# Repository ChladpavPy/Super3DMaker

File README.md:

# Super3DMaker Controller Board

So first I want to explain, why I started this project. I had an old Profi3DMaker 3D printer at home, which was not used for a long time, mainly because of the hardware, which was just outdated. Because the printer had electronics probably from years like 2012 and older, it was my idea to bring it again to life, because the tech of 3D printing and electronics changed a lot. The 3D printer actually works, but does not stand a chance to modern machines which would be even cheaper based on the materials. Back in 2012, this printer was high-end and one of the most expensive 3D printers, you could get, because of the high quality aluminium frame, but because the technology changed so rapidly, it is just unreliable and prints items badly now, when compared to new 3d printers, which are also cheap. And because it is mainly and electronics issue, I realized that I could build my own new 3D printer board for this 3D printer and bring it again to life, so I started new Project.

The first stage was actually reverse-engineering the old board and studying as much possible of how modern 3d printers work.

A custom mainboard designed to replace the old electronics in my 3D printer. Built to handle klipper high speed kinematics and communicate directly with a Raspberry Pi Zero 2W. Designed entirely from scratch in KiCad 10.

## The Build and Integration Phase

After receiving the manufactured PCB from JLCPCB, the project transitioned into the physical build phase. This involved soldering all components and integrating the new board into the chassis. 

The most intensive part was the software setup and calibration. I configured Klipper and the Raspberry Pi, and spent a significant amount of time getting the `printer.cfg` right. This meant dialing in the correct motor parameters, gear ratios, and microsteps through trial and error and reverse engineering.

### Results and Current Limitations

The custom STM32F407VET6 board works perfectly and successfully replaces the old ATmega setup. Klipper brings many modern features compared to the old Marlin firmware. Thanks to the new TMC2209 drivers, the printer is now significantly quieter during operation.

However, the build process revealed several mechanical limitations of the original Profi3DMaker chassis that the new electronics alone cannot fix:
* **Z-Axis Noise:** Despite the silent drivers, the Z-axis still makes mechanical grinding noises, indicating a physical issue with the leadscrews or bearings.
* **Heated Bed Inefficiency:** The massive original heated bed takes around an hour to reach just 70°C. 
* **Toolhead Weight:** The older extruder system is extremely heavy, limiting printing speeds and precision. 

To fully utilize the new controller board's capabilities, I have designed a completely new mount for a modern toolhead. This can be actually directly mounted on the chassis. However, this will only add weight if I don't disassemble the moving carriage from the tubes, which requires practically disassembling the entire printer, which I plan to do as a future upgrade. This would also require creating another model which would replace the previous aluminium carriage on the tubes. For now, the goal of successfully designing, building, and running a custom controller board has been achieved.

## Firmware

Since this board is built around a custom STM32F407VET6 microcontroller, it runs on the open-source [Klipper](https://github.com/Klipper3d/klipper) firmware. Instead of writing custom kinematic calculations from scratch, the firmware setup uses a printer configuration file. You can find the complete pin-mapping and configuration file (`printer.cfg`), along with the original dumped `.srec` firmware files used to reverse-engineer the correct gear ratios and microsteps, ready in the `Firmware` folder. You can also access all the other original files for this 3D printer by registering on the 3D Factories website.
## Project Features

* **Microcontroller:** STM32F407VET6 (100-pin, 32-bit ARM Cortex-M4)
* **Stackup:** 4-Layer PCB (Signal / GND / GND / Signal) for internal routing and better EMI shielding
* **Stepper Drivers:** 6x UART-controlled TMC2209 sockets
* **Power:** 24V main input with dual LM2596S buck converters (5V and 3.3V rails)
* **Connectivity:** USB-B for main communication, native Raspberry Pi UART interface
* **Displays:** Standard 10-pin IDC EXP1 and EXP2 headers for legacy 12864 or modern SPI BTT Mini12864 displays
* **Hardware Interlock:** Laser module power logically tied to the high-current heated bed circuit to prevent simultaneous power draw

* And more other...

### Video Demos

https://github.com/user-attachments/assets/c8a4d6e0-8937-4ded-b093-ac17ca0ef771

https://github.com/user-attachments/assets/72c90019-3e0b-4c00-92d0-47ec632bfb1b

https://github.com/user-attachments/assets/8aad29d0-d306-4471-a87c-c93d6b09ec2d

LIS2DW accelometer calibration

https://github.com/user-attachments/assets/c06aa969-909b-4192-8ba1-088b3594a9f0

CR Touch Bed Mesh

https://github.com/user-attachments/assets/029f4fde-3b9d-4758-a506-7faca7a6295e

## Gallery

### Build Preview

### Printing

### 3D PCB Render

### PCB Routing

### Schematic

---

## Bill of Materials (BOM)

| Component | Qty | Purpose / Description | Price (USD) | Link / Distributor |
| :--- | :---: | :--- | :--- | :--- |
| **Custom PCBA (Mainboard)** | 2 | Custom designed 4-layer STM32 controller board. Fully assembled via JLCPCB SMT (minus the THT USB-B connector which will be soldered manually to avoid mechanical case collisions). | ~$137.67 | JLCPCB - This is the price for 2 assembled boards to keep the price as low as possible. |
| **BIQU H2 V2S REVO** | 1 | Ultra-lightweight direct drive extrusion system with rapid-change nozzle capability. Replaces the current heavy toolhead, significantly reducing weight on the massive 400mm X-axis for faster, vibration-free printing. | $151.45 | [Allegro](https://allegro.cz/produkt/extruder-btt-biqu-h2-v2s-revo-direct-drive-1-75-mm-ce63ae7c-46b2-4eb6-95d3-a286495341f3?offerId=12801178318) |
| **ADXL345 3-Axis Accelerometer** | 2 | Essential for Klipper's Input Shaping calibration. It measures the physical resonance frequencies of the X and Y axes, allowing the firmware to actively cancel out vibrations during high-speed printing and eliminate ringing/ghosting on the printed parts. | $2.88 | [AliExpress](https://a.aliexpress.com/_EH7aAa2) |
| **CR-Touch (Auto Bed Leveling)** | 1 | Provides automatic high-precision mesh bed leveling. It compensates for any slight warping of the print bed and ensures a perfect first layer every time by measuring the distance between the nozzle and the build surface at multiple points. | $20.00 | [AliExpress](https://a.aliexpress.com/_EvwN6HC) |
| **BigTreeTech TMC2209 V1.3** | 6 | These are high-performance silent motor drivers required for the custom motherboard. They feature StealthChop technology for near-silent operation and StallGuard for sensorless homing, eliminating the need for physical limit switches. | $19.25 | [AliExpress](https://a.aliexpress.com/_EILgKrG) |
| **Raspberry Pi Zero 2W** | 1 | Serves as the main host computer for the custom 3D printer. It runs the Klipper firmware ecosystem and its web interface (Mainsail/Fluidd), performs heavy kinematics calculations, and sends precise hardware commands to the custom-designed STM32 motherboard via serial/USB connection. | $20.17 | [Rpishop](https://rpishop.cz/raspberry-pi-zero/4311-raspberry-pi-zero-2-w.html) |

### Mechanical and Assembly

| Item | Qty | Specification | Purpose |
| :--- | :---: | :--- | :--- |
| **Original Aluminum Case** | 1 | The heavy original printer chassis | I had to reverse engineer the mounting holes and connector distances, because I could not get the original CAD files. It was a nightmare but it fits within like 4.7mm of the board edge now. |
| **M3 Screws** | 4 | Standard mounting hardware | Securing the PCB to the chassis standoffs. |
- For the case of the 3d printer - Profi3DMaker case is used

## How to Build and Flash Firmware

If you want to replicate this custom controller board for your own Profi3DMaker or similar 3D printer, follow these steps:

1. **PCB Fabrication & Assembly:** Use the provided Gerber files (found in the repository) to manufacture the board. Most SMD components are assembled by JLCPCB, but you will need to manually solder the THT USB-B connector, terminal blocks, and JST headers.
2. **STM32 Bootloader & Klipper Firmware:**
   * Connect the board to your PC via USB-B while holding the BOOT/RESET buttons to enter DFU mode.
   * Compile Klipper for the `STM32F407VET6` chip using `make menuconfig` on your Raspberry Pi Zero 2W.
   * Flash the compiled `klipper.bin` to the STM32 using STM32CubeProgrammer.
3. **Raspberry Pi Integration:** Connect the Raspberry Pi Zero 2W to the board using the dedicated UART pins for serial communication.
4. **Configuration:** Upload the provided `printer.cfg` (found in the `/Firmware` folder) to your Klipper interface (Mainsail/Fluidd) and verify motor directions and sensor readings.
That is all, thank you for reading!

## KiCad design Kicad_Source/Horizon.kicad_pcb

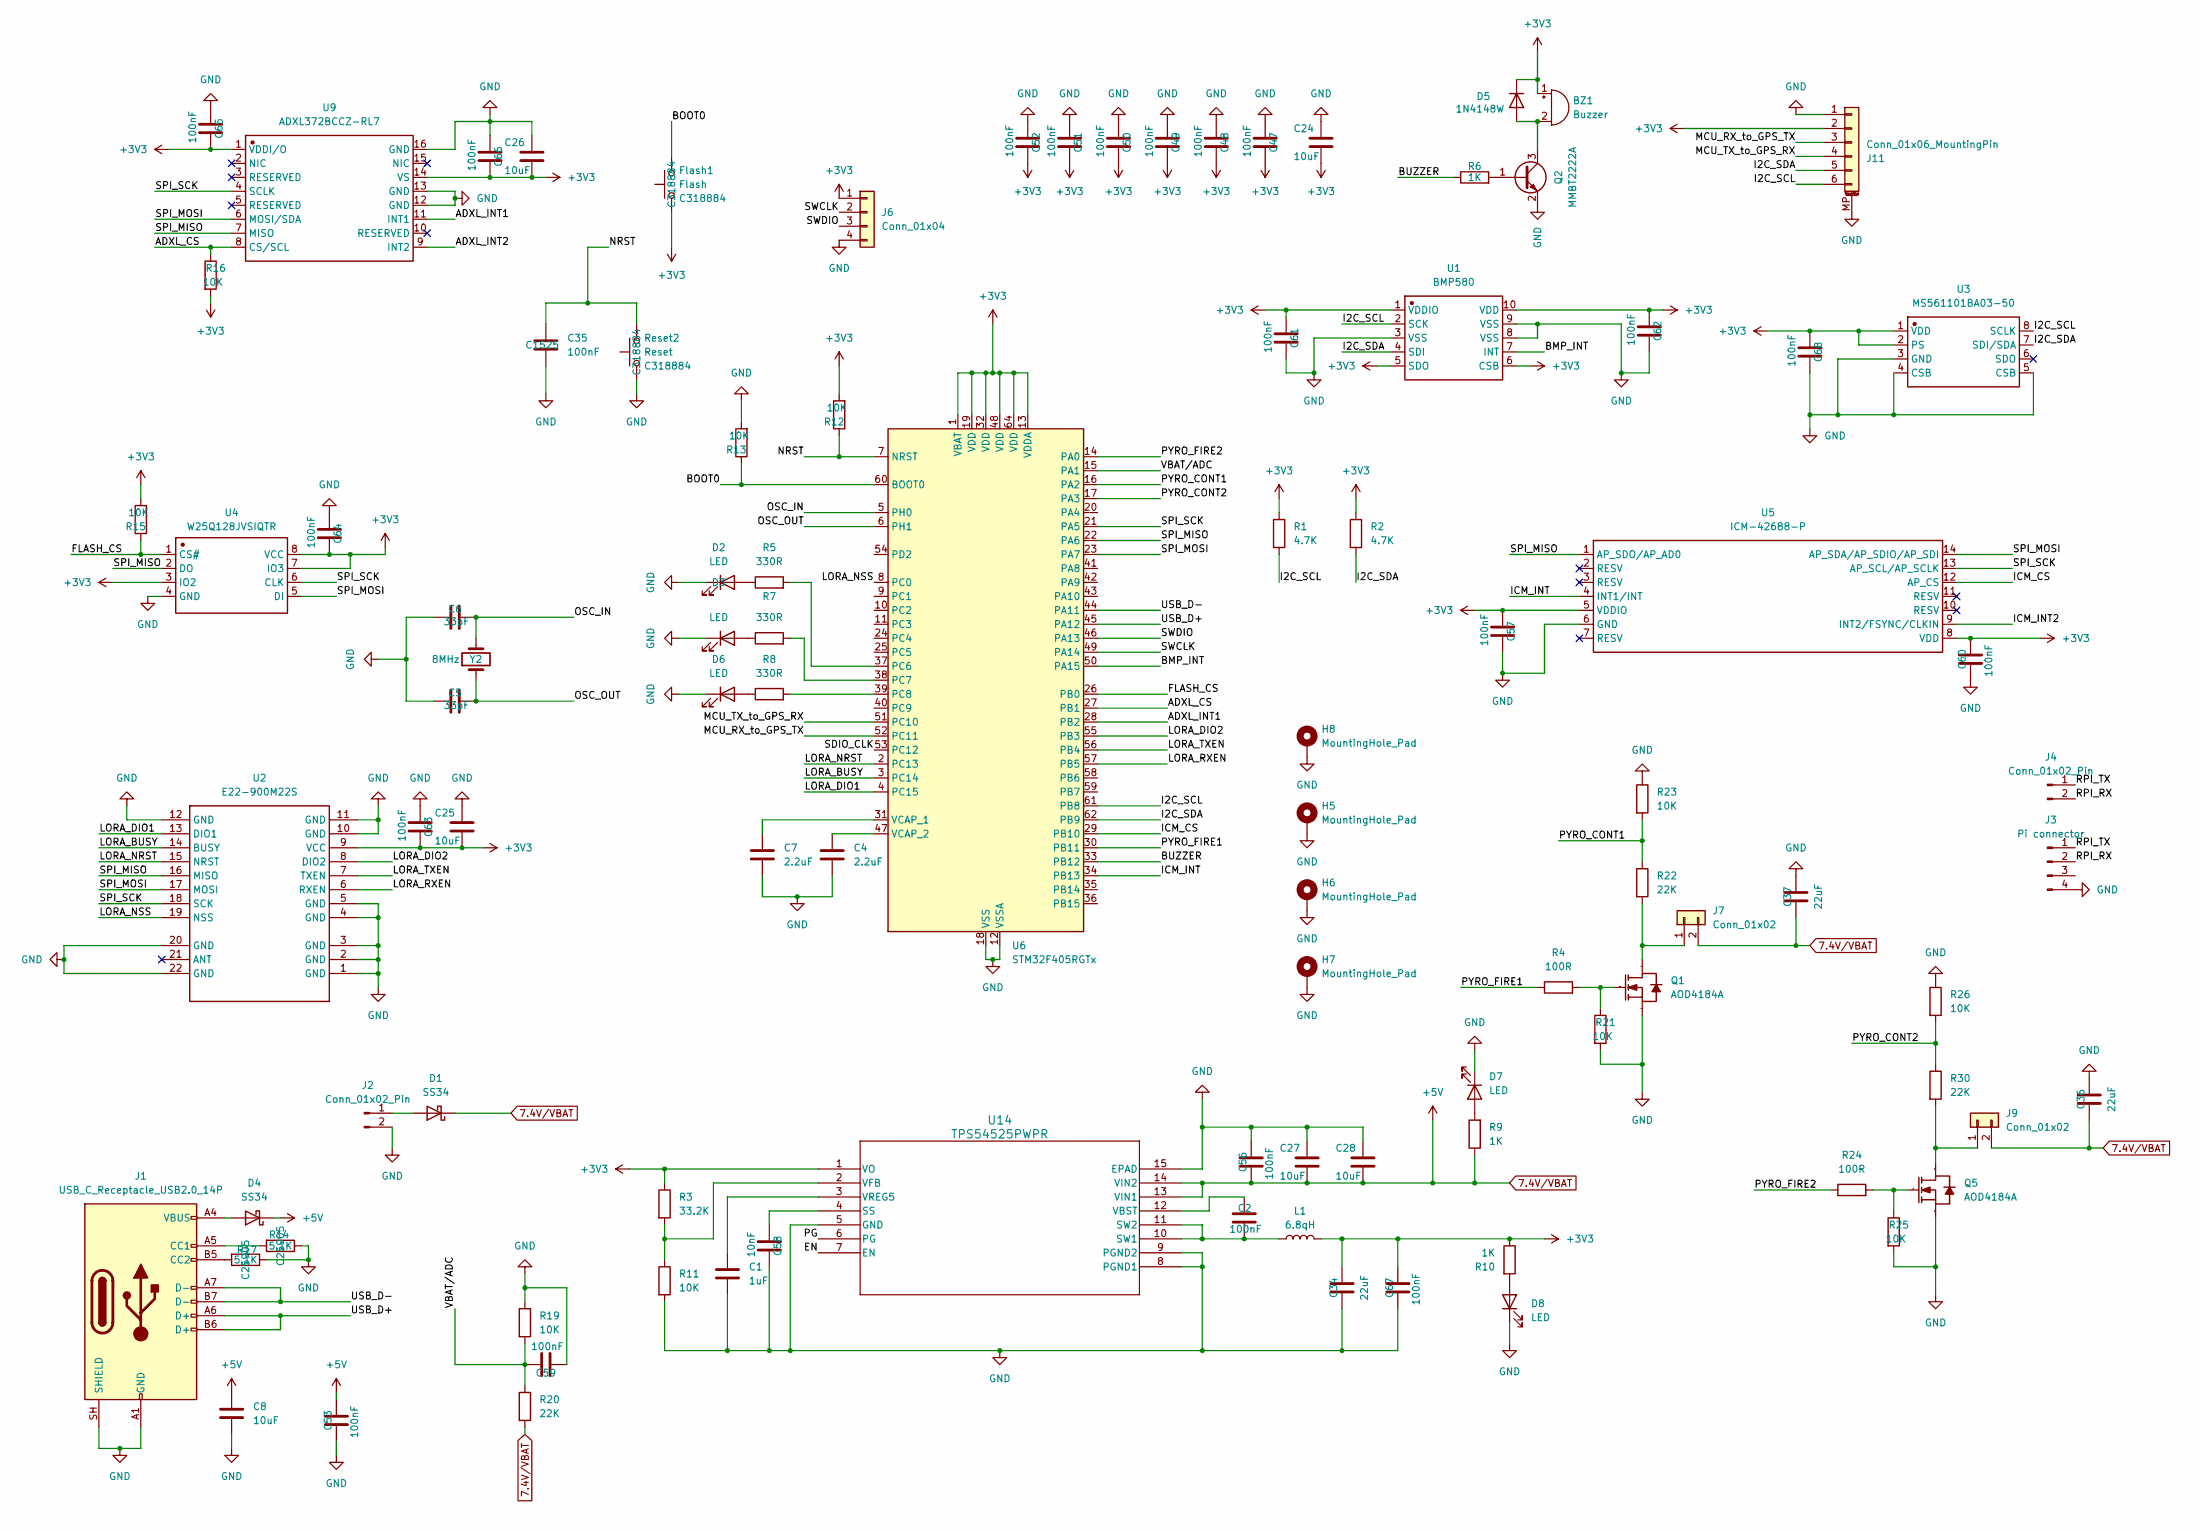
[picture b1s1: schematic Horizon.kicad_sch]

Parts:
BZ1: Buzzer; BUZ-SMD_4P-L8.5-W8.5-P8.50-TL; LCSC C95298
C1: 1uF; C_0402_1005Metric; LCSC C52923
C2, C47, C48, C49, C50, C51, C52, C53, C56, C57, C59, C60, C61, C62, C63, C64, C65, C66, C67, C68: 100nF; C_0402_1005Metric; LCSC C307331
C4, C7: 2.2uF; C_0603_1608Metric; LCSC C23630
C5, C6: 33pF; C_0402_1005Metric; LCSC C1562
C8: 10uF; C_0603_1608Metric; LCSC C96446
C24, C27, C28: 10uF; C_0805_2012Metric; MNF PART NUMBER C15850; LCSC C15850
C25, C26: 10uF; C_0603_1608Metric; MNF PART NUMBER C19702; LCSC C19702
C34, C36, C37: 22uF; C_0805_2012Metric; LCSC C45783
C35: 100nF; C_0402_1005Metric; MNF PART NUMBER C1525; LCSC C1525
C58: 10nF; C_0402_1005Metric; LCSC C15195
D1, D4: SS34; SMA_L4.3-W2.6-LS5.2-RD; LCSC C8678
D2, D7, D8: LED; LED_0603_1608Metric; LCSC C2286
D3: LED; LED_0603_1608Metric; LCSC C2288
D5: 1N4148W; D_SOD-123; LCSC C81598
D6: LED; LED_0603_1608Metric; LCSC C12624
Flash1: Flash; SW_Push_1P1T_XKB_TS-1187A; MNF PART NUMBER C318884; LCSC C318884
H5, H6, H7, H8: MountingHole_Pad; MountingHole_3.2mm_M3_Pad_Via
J1: USB_C_Receptacle_USB2.0_14P; USB_C_Receptacle_HCTL_HC-TYPE-C-16P-01A; LCSC C19274016
J2: Conn_01x02_Pin; AMASS_XT30UPB-M_1x02_P5.0mm_Vertical; LCSC C428721
J3: Pi connector
J4: Conn_01x02_Pin
J6: Conn_01x04; PinHeader_1x04_P2.54mm_Vertical
J7, J9: Conn_01x02; Molex_Micro-Fit_3.0_43045-0212_2x01_P3.00mm_Vertical
J11: Conn_01x06_MountingPin; JST_SH_SM06B-SRSS-TB_1x06-1MP_P1.00mm_Horizontal
L1: 6.8qH; IND-SMD_L6.0-W6.0_SWPA6045S; LCSC C57254
Q1, Q5: AOD4184A; TO-252-2_L6.6-W6.1-P4.57-LS9.9-TL-CW; Manufacturer Part AOD4184A; LCSC C99124
Q2: MMBT2222A; SOT-23; LCSC C8512
R1, R2: 4.7K; R_0402_1005Metric; LCSC C25900
R3: 33.2K; R_0402_1005Metric; LCSC C850963
R4, R24: 100R; C_0402_1005Metric; LCSC C25076
R5, R7, R8: 330R; R_0402_1005Metric; LCSC C25104
R6, R9, R10: 1K; R_0402_1005Metric; LCSC C11702
R11, R25: 10K; R_0402_1005Metric; LCSC C25804
R12, R13, R15, R16, R21: 10K; R_0402_1005Metric; LCSC C25744
R14, R17: 5.1K; R_0402_1005Metric; MNF PART NUMBER C25905; LCSC C25905
R19, R23, R26: 10K; C_0402_1005Metric; LCSC C25744
R20, R22, R30: 22K; C_0402_1005Metric; LCSC C25768
Reset2: Reset; SW_Push_1P1T_XKB_TS-1187A; MNF PART NUMBER C318884; LCSC C318884
U1: BMP580; LGA-10_L2.0-W2.0-P0.50-TL_BMP580; Manufacturer Part BMP580; LCSC C22391138
U2: E22-900M22S; WIRELM-SMD_E22-900M22S; Manufacturer Part E22-900M22S; LCSC C411293
U3: MS561101BA03-50; SENSORS-SMD_MS5611-01BA03; Manufacturer Part MS561101BA03-50
U4: W25Q128JVSIQTR; SOIC-8_L5.3-W5.3-P1.27-LS8.0-BL; Manufacturer Part W25Q128JVSIQ; LCSC C97521
U5: ICM-42688-P; LGA-14_L3.0-W2.5-P0.50-TL; Manufacturer Part ICM-42688-P; LCSC C1850418
U6: STM32F405RGTx; LQFP-64_10x10mm_P0.5mm; LCSC C15742
U9: ADXL372BCCZ-RL7; LGA-16_L3.3-W3.0-P0.50-TL; Manufacturer Part ADXL372BCCZ-RL7; LCSC C579465
U14: TPS54525PWPR; TSSOP-14_L5.0-W4.4-P0.65-LS6.4-BL-EP; LCSC C140350
Y2: 8MHz; Crystal_SMD_5032-2Pin_5.0x3.2mm; LCSC C115962

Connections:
7.4V/VBAT: C8.1, C27.2, C28.2, C36.2, C37.2, C53.1, C56.2, D1.1 (K), D4.1 (K), J7.2, J9.2, R9.1, R20.2, U14.13 (VIN1), U14.14 (VIN2)
+3V3: BZ1.1 (+), C24.2, C25.2, C26.2, C34.1, C47.1, C48.1, C49.1, C50.1, C51.1, C52.1, C57.2, C60.1, C61.2, C62.2, C63.1, C64.1, C65.1, C66.1, C67.1, C68.2, D5.1 (K), Flash1.1, J6.1, J11.2, L1.2, R1.1, R2.1, R3.1, R10.1, R12.2, R15.2, R16.2, U1.1 (VDDIO), U1.5 (SDO), U1.6 (CSB), U1.10 (VDD), U2.9 (VCC), U3.1 (VDD), U3.2 (PS), U4.3 (IO2), U4.7 (IO3), U4.8 (VCC), U5.5 (VDDIO), U5.8 (VDD), U6.1 (VBAT), U6.13 (VDDA), U6.19 (VDD), U6.32 (VDD), U6.48 (VDD), U6.64 (VDD), U9.1 (VDDI/O), U9.14 (VS), U14.1 (VO)
/ADXL_CS: R16.1, U6.27 (PB1), U9.8 (CS/SCL)
/ADXL_INT1: U6.28 (PB2), U9.11 (INT1)
/ADXL_INT2: U9.9 (INT2)
/BMP_INT: U1.7 (INT), U6.50 (PA15)
/BOOT0: Flash1.2, R13.1, U6.60 (BOOT0)
/BUZZER: R6.1, U6.33 (PB12)
/EN: U14.7 (EN)
/FLASH_CS: R15.1, U4.1 (CS#), U6.26 (PB0)
/I2C_SCL: J11.6, R1.2, U1.2 (SCK), U3.8 (SCLK), U6.61 (PB8)
/I2C_SDA: J11.5, R2.2, U1.4 (SDI), U3.7 (SDI/SDA), U6.62 (PB9)
/ICM_CS: U5.12 (AP_CS), U6.29 (PB10)
/ICM_INT: U5.4 (INT1/INT), U6.34 (PB13)
/ICM_INT2: U5.9 (INT2/FSYNC/CLKIN)
/LORA_BUSY: U2.14 (BUSY), U6.3 (PC14)
/LORA_DIO1: U2.13 (DIO1), U6.4 (PC15)
/LORA_DIO2: U2.8 (DIO2), U6.55 (PB3)
/LORA_NRST: U2.15 (NRST), U6.2 (PC13)
/LORA_NSS: U2.19 (NSS), U6.8 (PC0)
/LORA_RXEN: U2.6 (RXEN), U6.57 (PB5)
/LORA_TXEN: U2.7 (TXEN), U6.56 (PB4)
/MCU_RX_to_GPS_TX: J11.3, U6.52 (PC11)
/MCU_TX_to_GPS_RX: J11.4, U6.51 (PC10)
/NRST: C35.1, R12.1, Reset2.2, U6.7 (NRST)
/OSC_IN: C6.1, U6.5 (PH0), Y2.2
/OSC_OUT: C5.1, U6.6 (PH1), Y2.1
/PG: U14.6 (PG)
/PYRO_CONT1: R22.1, R23.2, U6.16 (PA2)
/PYRO_CONT2: R26.2, R30.1, U6.17 (PA3)
/PYRO_FIRE1: R4.1, U6.30 (PB11)
/PYRO_FIRE2: R24.1, U6.14 (PA0)
/SDIO_CLK: U6.53 (PC12)
/SPI_MISO: U2.16 (MISO), U4.2 (DO), U5.1 (AP_SDO/AP_AD0), U6.22 (PA6), U9.7 (MISO)
/SPI_MOSI: U2.17 (MOSI), U4.5 (DI), U5.14 (AP_SDA/AP_SDIO/AP_SDI), U6.23 (PA7), U9.6 (MOSI/SDA)
/SPI_SCK: U2.18 (SCK), U4.6 (CLK), U5.13 (AP_SCL/AP_SCLK), U6.21 (PA5), U9.4 (SCLK)
/SWCLK: J6.2, U6.49 (PA14)
/SWDIO: J6.3, U6.46 (PA13)
/USB_D+: J1.A6 (D+), J1.B6 (D+), U6.45 (PA12)
/USB_D-: J1.A7 (D-), J1.B7 (D-), U6.44 (PA11)
/VBAT/ADC: C59.1, R19.2, R20.1, U6.15 (PA1)
GND: C1.2, C4.1, C5.2, C6.2, C7.1, C8.2, C24.1, C25.1, C26.1, C27.1, C28.1, C34.2, C35.2, C36.1, C37.1, C47.2, C48.2, C49.2, C50.2, C51.2, C52.2, C53.2, C56.1, C57.1, C58.1, C59.2, C60.2, C61.1, C62.1, C63.2, C64.2, C65.2, C66.2, C67.2, C68.1, D2.1 (K), D3.1 (K), D6.1 (K), D7.1 (K), D8.1 (K), H5.1 (1_1), H6.1 (1_1), H7.1 (1_1), H8.1 (1_1), J1.A1 (GND), J1.A12 (GND), J1.B1 (GND), J1.B12 (GND), J1.SH (SHIELD), J2.2, J3.4, J6.4, J11.1, J11.MP (MountPin), Q1.3 (S), Q2.2 (E), Q5.3 (S), R11.2, R13.2, R14.1, R17.1, R19.1, R21.2, R23.1, R25.2, R26.1, Reset2.1, U1.3 (VSS), U1.8 (VSS), U1.9 (VSS), U2.1 (GND), U2.2 (GND), U2.3 (GND), U2.4 (GND), U2.5 (GND), U2.10 (GND), U2.11 (GND), U2.12 (GND), U2.20 (GND), U2.22 (GND), U3.3 (GND), U3.4 (CSB), U3.5 (CSB), U4.4 (GND), U5.6 (GND), U6.12 (VSSA), U6.18 (VSS), U6.63 (VSS), U9.12 (GND), U9.13 (GND), U9.16 (GND), U14.5 (GND), U14.8 (PGND1), U14.9 (PGND2), U14.15 (EPAD)
unnamed: BZ1.2 (-), D5.2 (A), Q2.3 (C)
unnamed: D1.2 (A), J2.1
unnamed: D2.2 (A), R5.1
unnamed: D3.2 (A), R7.1
unnamed: D4.2 (A), J1.A4 (VBUS), J1.A9 (VBUS), J1.B4 (VBUS), J1.B9 (VBUS)
unnamed: D6.2 (A), R8.1
unnamed: D7.2 (A), R9.2
unnamed: D8.2 (A), R10.2
unnamed: J1.A5 (CC1), R14.2
unnamed: J1.B5 (CC2), R17.2
unnamed: J3.1, J4.1
unnamed: J3.2, J4.2
unnamed: J7.1, Q1.2 (D), R22.2
unnamed: J9.1, Q5.2 (D), R30.2
unnamed: Q1.1 (G), R4.2, R21.1
unnamed: Q2.1 (B), R6.2
unnamed: Q5.1 (G), R24.2, R25.1
unnamed: R5.2, U6.37 (PC6)
unnamed: R7.2, U6.38 (PC7)
unnamed: R8.2, U6.39 (PC8)
unnamed: C7.2, U6.31 (VCAP_1)
unnamed: C4.2, U6.47 (VCAP_2)
unnamed: C58.2, U14.4 (SS)
unnamed: C2.2, L1.1, U14.10 (SW1), U14.11 (SW2)
unnamed: C2.1, U14.12 (VBST)
unnamed: R3.2, R11.1, U14.2 (VFB)
unnamed: C1.1, U14.3 (VREG5)

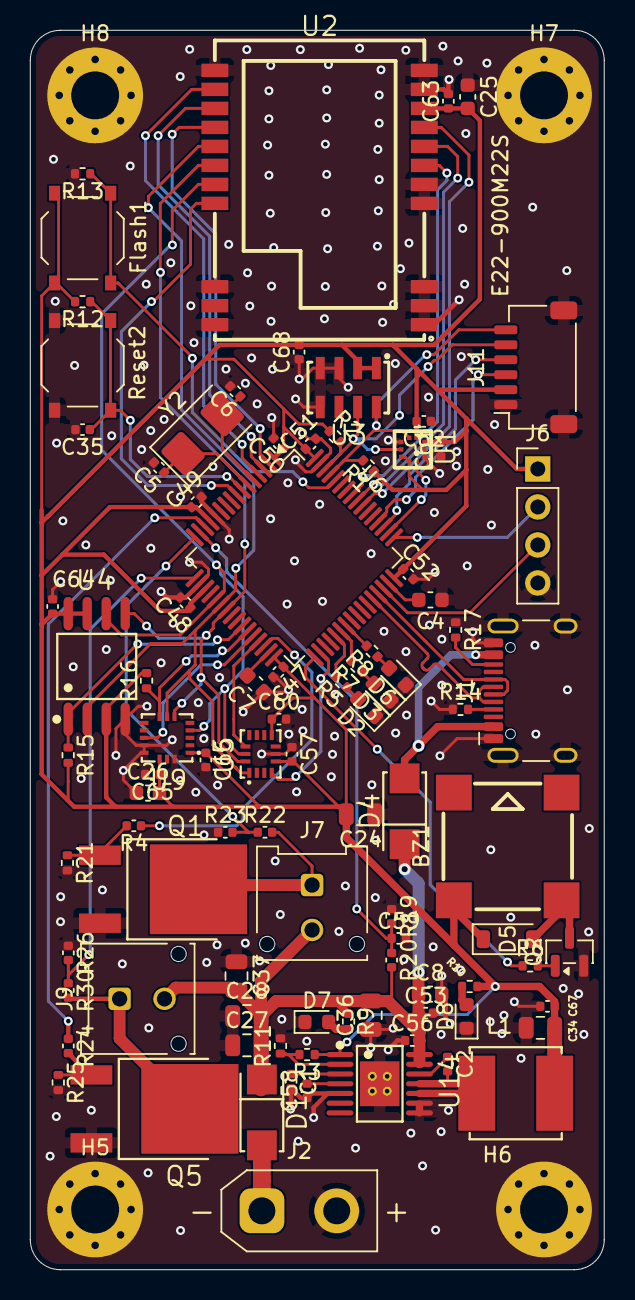
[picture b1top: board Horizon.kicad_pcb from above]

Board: 4 copper layers, 38.4 x 82.8 mm, 96 parts (0 on the bottom side), 62 nets.
